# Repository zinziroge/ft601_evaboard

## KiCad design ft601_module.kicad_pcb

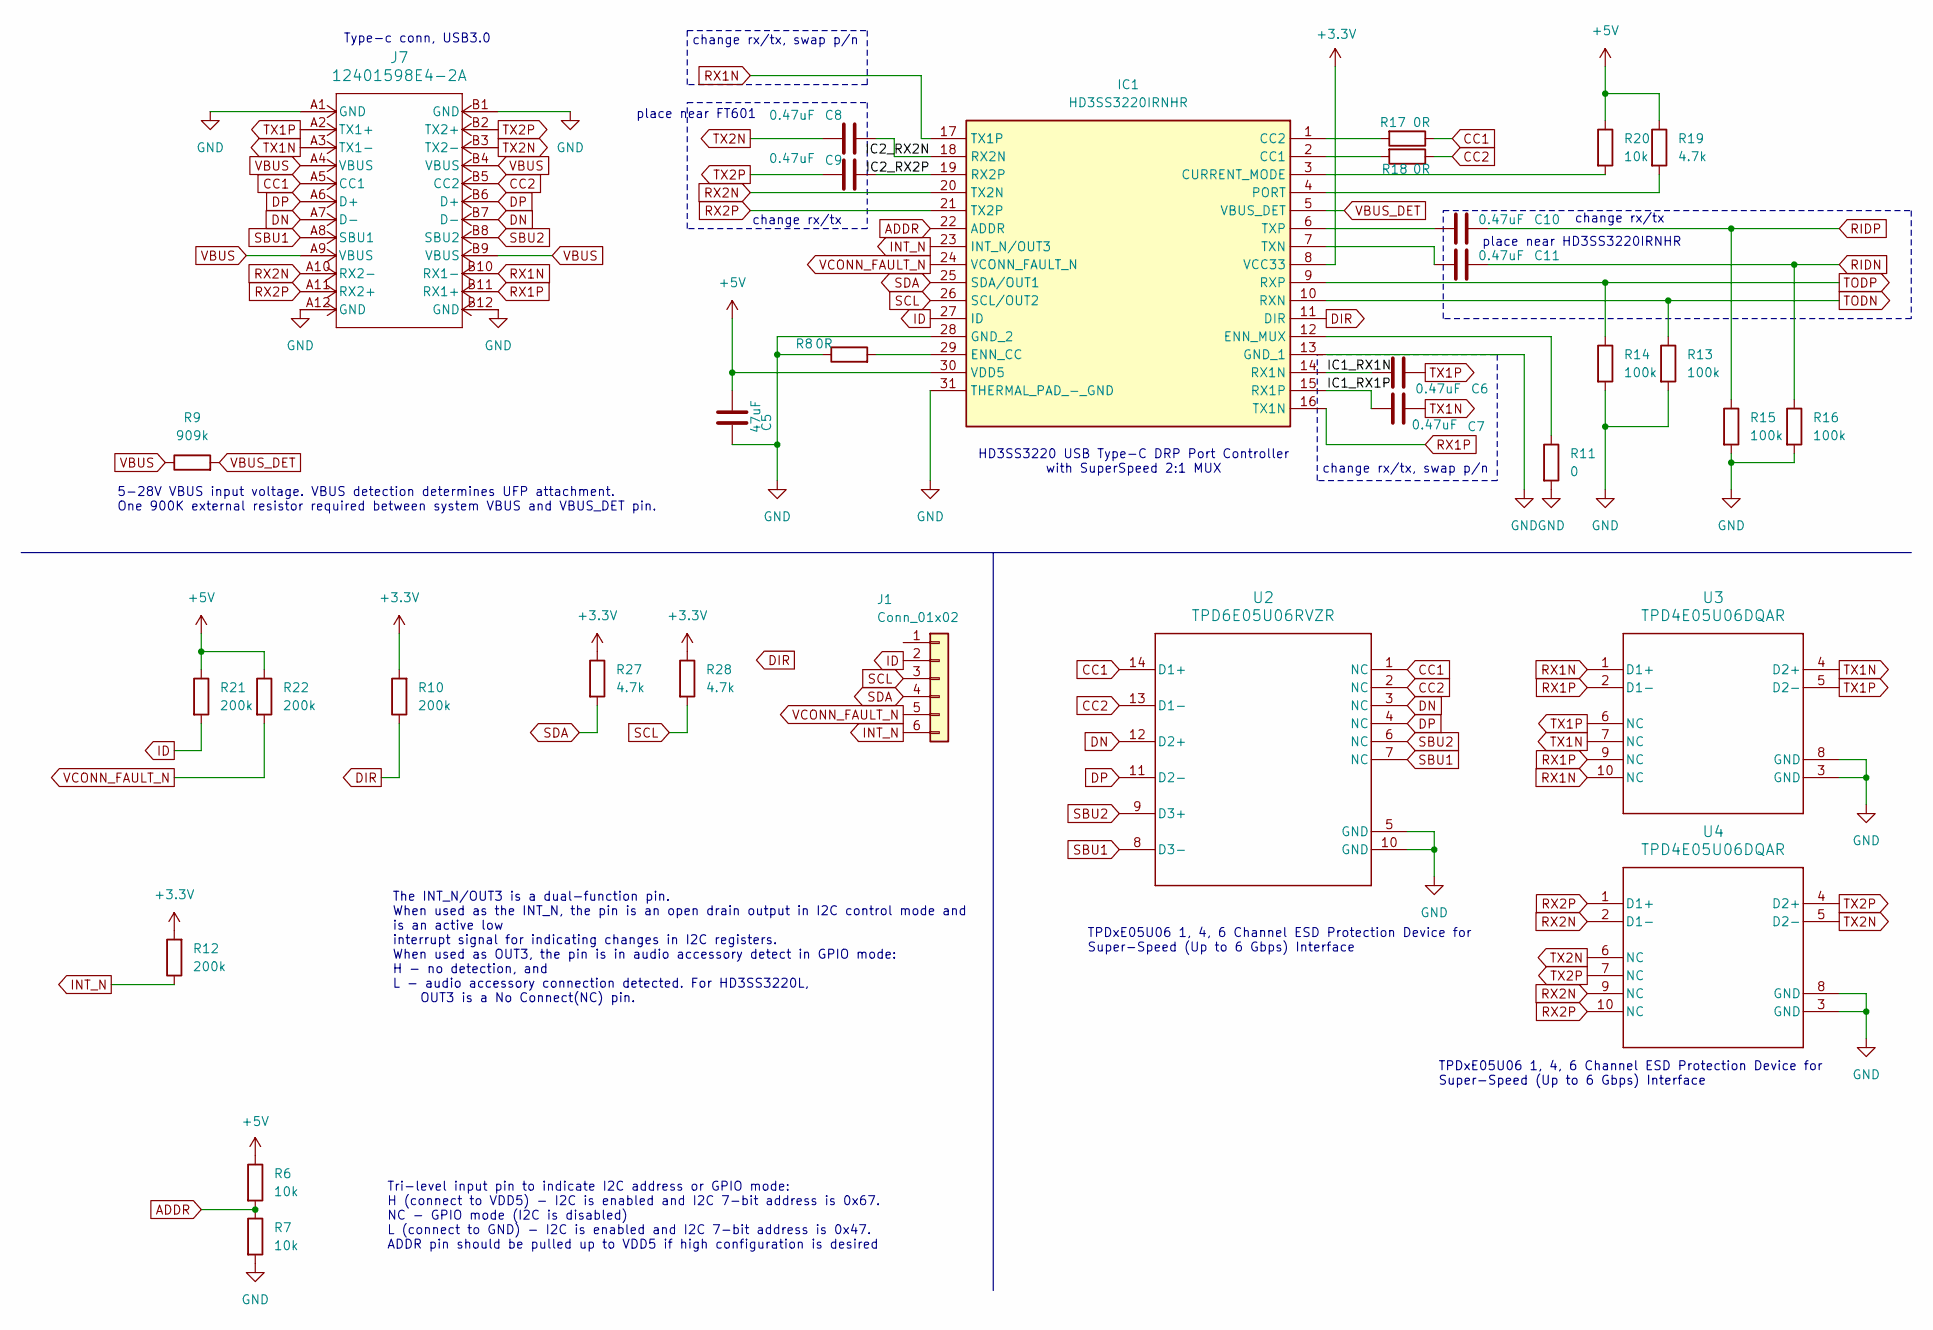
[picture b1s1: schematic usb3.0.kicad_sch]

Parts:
C5: 47uF; C_0603_1608Metric
C6, C7, C8, C9, C10, C11: 0.47uF; C_0402_1005Metric
IC1: HD3SS3220IRNHR; Manufacturer_Part_Number HD3SS3220IRNHR; Mouser Part Number 595-HD3SS3220IRNHR
J1: Conn_01x02; PinHeader_1x06_P2.54mm_Vertical
J7: 12401598E4-2A; CONN_12401598E4-2A_AMP
R6, R7, R20: 10k; R_0603_1608Metric
R8, R17, R18: 0R; R_0603_1608Metric
R9: 909k; R_0603_1608Metric
R10, R12, R21, R22: 200k; R_0603_1608Metric
R11: 0; R_0603_1608Metric
R13, R14, R15, R16: 100k; R_0603_1608Metric
R19, R27, R28: 4.7k; R_0603_1608Metric
U2: TPD6E05U06RVZR; RVZ0014A
U3, U4: TPD4E05U06DQAR; DQA0010A

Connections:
+3.3V: IC1.8 (VCC33), R10.2, R12.2, R27.1, R28.1; also elsewhere on the board
+5V: C5.1, IC1.30 (VDD5), R6.1, R19.1, R20.1, R21.1, R22.1; also elsewhere on the board
/usb3.0/IC1_RX1N: C6.2, IC1.14 (RX1N)
/usb3.0/IC1_RX1P: C7.2, IC1.15 (RX1P)
/usb3.0/IC2_RX2N: C8.1, IC1.18 (RX2N)
/usb3.0/IC2_RX2P: C9.1, IC1.19 (RX2P)
ADDR: IC1.22 (ADDR), R6.2, R7.1
CC1: J7.A5 (CC1), R17.1, U2.1 (NC), U2.14 (D1+)
CC2: J7.B5 (CC2), R18.1, U2.2 (NC), U2.13 (D1-)
DIR: IC1.11 (DIR), R10.1
DN: J7.A7 (D-), J7.B7 (D-), U2.3 (NC), U2.12 (D2+); also elsewhere on the board
DP: J7.A6 (D+), J7.B6 (D+), U2.4 (NC), U2.11 (D2-); also elsewhere on the board
GND: C5.2, IC1.13 (GND_1), IC1.28 (GND_2), IC1.31 (THERMAL_PAD_-_GND), J7.A1 (GND), J7.A12 (GND), J7.B1 (GND), J7.B12 (GND), R7.2, R8.1, R11.2, R13.2, R14.2, R15.2, R16.2, U2.5 (GND), U2.10 (GND), U3.3 (GND), U3.8 (GND), U4.3 (GND), U4.8 (GND); also elsewhere on the board
ID: IC1.27 (ID), J1.2, R21.2
INT_N: IC1.23 (INT_N/OUT3), J1.6, R12.1
unnamed: IC1.2 (CC1), R18.2
unnamed: IC1.1 (CC2), R17.2
unnamed: IC1.3 (CURRENT_MODE), R20.2
unnamed: IC1.29 (ENN_CC), R8.2
unnamed: IC1.12 (ENN_MUX), R11.1
unnamed: IC1.4 (PORT), R19.2
unnamed: C11.2, IC1.7 (TXN)
unnamed: C10.2, IC1.6 (TXP)
RIDN: C11.1, R16.1; also elsewhere on the board
RIDP: C10.1, R15.1; also elsewhere on the board
RX1N: IC1.17 (TX1P), J7.B10 (RX1-), U3.1 (D1+), U3.10 (NC)
RX1P: IC1.16 (TX1N), J7.B11 (RX1+), U3.2 (D1-), U3.9 (NC)
RX2N: IC1.20 (TX2N), J7.A10 (RX2-), U4.2 (D1-), U4.9 (NC)
RX2P: IC1.21 (TX2P), J7.A11 (RX2+), U4.1 (D1+), U4.10 (NC)
SBU1: J7.A8 (SBU1), U2.7 (NC), U2.8 (D3-)
SBU2: J7.B8 (SBU2), U2.6 (NC), U2.9 (D3+)
SCL: IC1.26 (SCL/OUT2), J1.3, R28.2
SDA: IC1.25 (SDA/OUT1), J1.4, R27.2
TODN: IC1.10 (RXN), R13.1; also elsewhere on the board
TODP: IC1.9 (RXP), R14.1; also elsewhere on the board
TX1N: C7.1, J7.A3 (TX1-), U3.4 (D2+), U3.7 (NC)
TX1P: C6.1, J7.A2 (TX1+), U3.5 (D2-), U3.6 (NC)
TX2N: C8.2, J7.B3 (TX2-), U4.5 (D2-), U4.6 (NC)
TX2P: C9.2, J7.B2 (TX2+), U4.4 (D2+), U4.7 (NC)
VBUS: J7.A4 (VBUS), J7.A9 (VBUS), J7.B4 (VBUS), J7.B9 (VBUS), R9.1; also elsewhere on the board
VBUS_DET: IC1.5 (VBUS_DET), R9.2
VCONN_FAULT_N: IC1.24 (VCONN_FAULT_N), J1.5, R22.2

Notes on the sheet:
place near FT601
HD3SS3220 USB Type-C DRP Port Controller with SuperSpeed 2:1 MUX
change rx/tx, swap p/n
5-28V VBUS input voltage. VBUS detection determines UFP attachment. One 900K external resistor required between system VBUS and VBUS_DET pin.
The INT_N/OUT3 is a dual-function pin. When used as the INT_N, the pin is an open drain output in I2C control mode and is an active low interrupt signal for indicating changes in I2C registers. When used as OUT3, the pin is in audio accessory detect in GPIO mode: H - no detection, and L - audio acc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
change rx/tx
TPDxE05U06 1, 4, 6 Channel ESD Protection Device for Super-Speed (Up to 6 Gbps) Interface
Tri-level input pin to indicate I2C address or GPIO mode: H (connect to VDD5) - I2C is enabled and I2C 7-bit address is 0x67. NC - GPIO mode (I2C is disabled) L (connect to GND) - I2C is enabled and I2C 7-bit address is 0x47. ADDR pin should be pulled up to VDD5 if high configuration is desired
Type-c conn, USB3.0
place near HD3SS3220IRNHR
TPDxE05U06 1, 4, 6 Channel ESD Protection Device for Super-Speed (Up to 6 Gbps) Interface

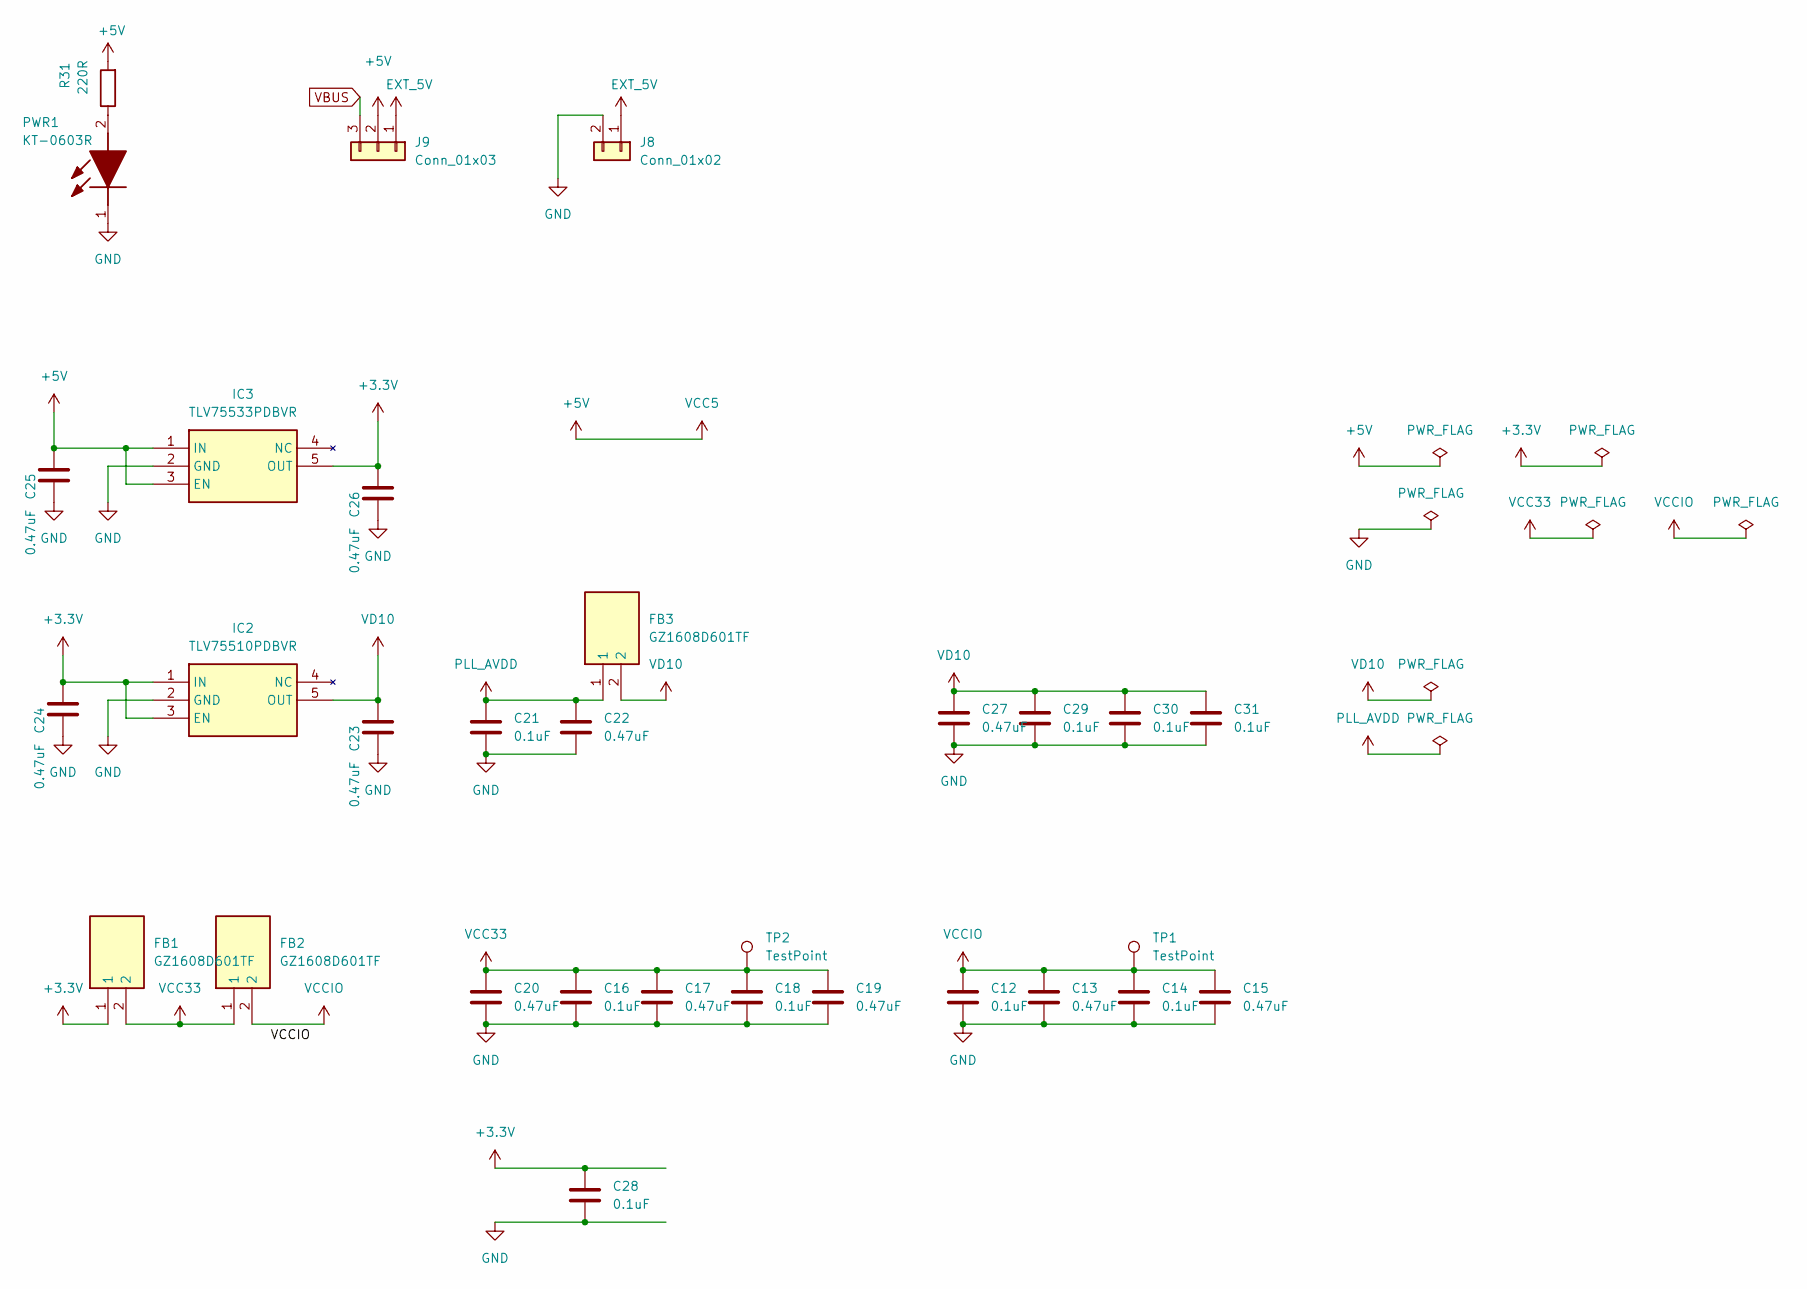
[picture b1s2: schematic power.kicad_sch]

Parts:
C12, C14, C16, C18, C21, C28, C29, C30, C31: 0.1uF; C_0603_1608Metric
C13, C15, C17, C19, C20, C22, C27: 0.47uF; C_0603_1608Metric
C23, C24, C25, C26: 0.47uF; C_0402_1005Metric
FB1, FB2, FB3: GZ1608D601TF; BEADC1608X95N; Manufacturer_Part_Number GZ1608D601TF
IC2: TLV75510PDBVR; SOT95P280X145-5N; Manufacturer_Part_Number TLV75510PDBVR; Mouser Part Number 595-TLV75510PDBVR
IC3: TLV75533PDBVR; SOT95P280X145-5N; Manufacturer_Part_Number TLV75533PDBVR; Mouser Part Number 595-TLV75533PDBVR
J8: Conn_01x02; PinHeader_1x02_P2.54mm_Vertical
J9: Conn_01x03; PinSocket_1x03_P2.54mm_Vertical
PWR1: KT-0603R; LEDC1608X70N; Manufacturer_Part_Number KT-0603R
R31: 220R; R_0603_1608Metric
TP1, TP2: TestPoint; TestPoint_Pad_D1.5mm

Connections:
+3.3V: C24.1, C26.1, C28.1, FB1.1, IC2.1 (IN), IC2.3 (EN), IC3.5 (OUT); also elsewhere on the board
+5V: C25.1, IC3.1 (IN), IC3.3 (EN), J9.2, R31.2; also elsewhere on the board
EXT_5V: J8.1, J9.1
GND: C12.2, C13.2, C14.2, C15.2, C16.2, C17.2, C18.2, C19.2, C20.2, C21.2, C22.2, C23.2, C24.2, C25.2, C26.2, C27.2, C28.2, C29.2, C30.2, C31.2, IC2.2 (GND), IC3.2 (GND), J8.2, PWR1.1 (K); also elsewhere on the board
unnamed: PWR1.2 (A), R31.1
PLL_AVDD: C21.1, C22.1, FB3.1; also elsewhere on the board
VBUS: J9.3; also elsewhere on the board
VCC33: C16.1, C17.1, C18.1, C19.1, C20.1, FB1.2, FB2.1, TP2.1; also elsewhere on the board
VCCIO: C12.1, C13.1, C14.1, C15.1, FB2.2, TP1.1; also elsewhere on the board
VD10: C23.1, C27.1, C29.1, C30.1, C31.1, FB3.2, IC2.5 (OUT); also elsewhere on the board

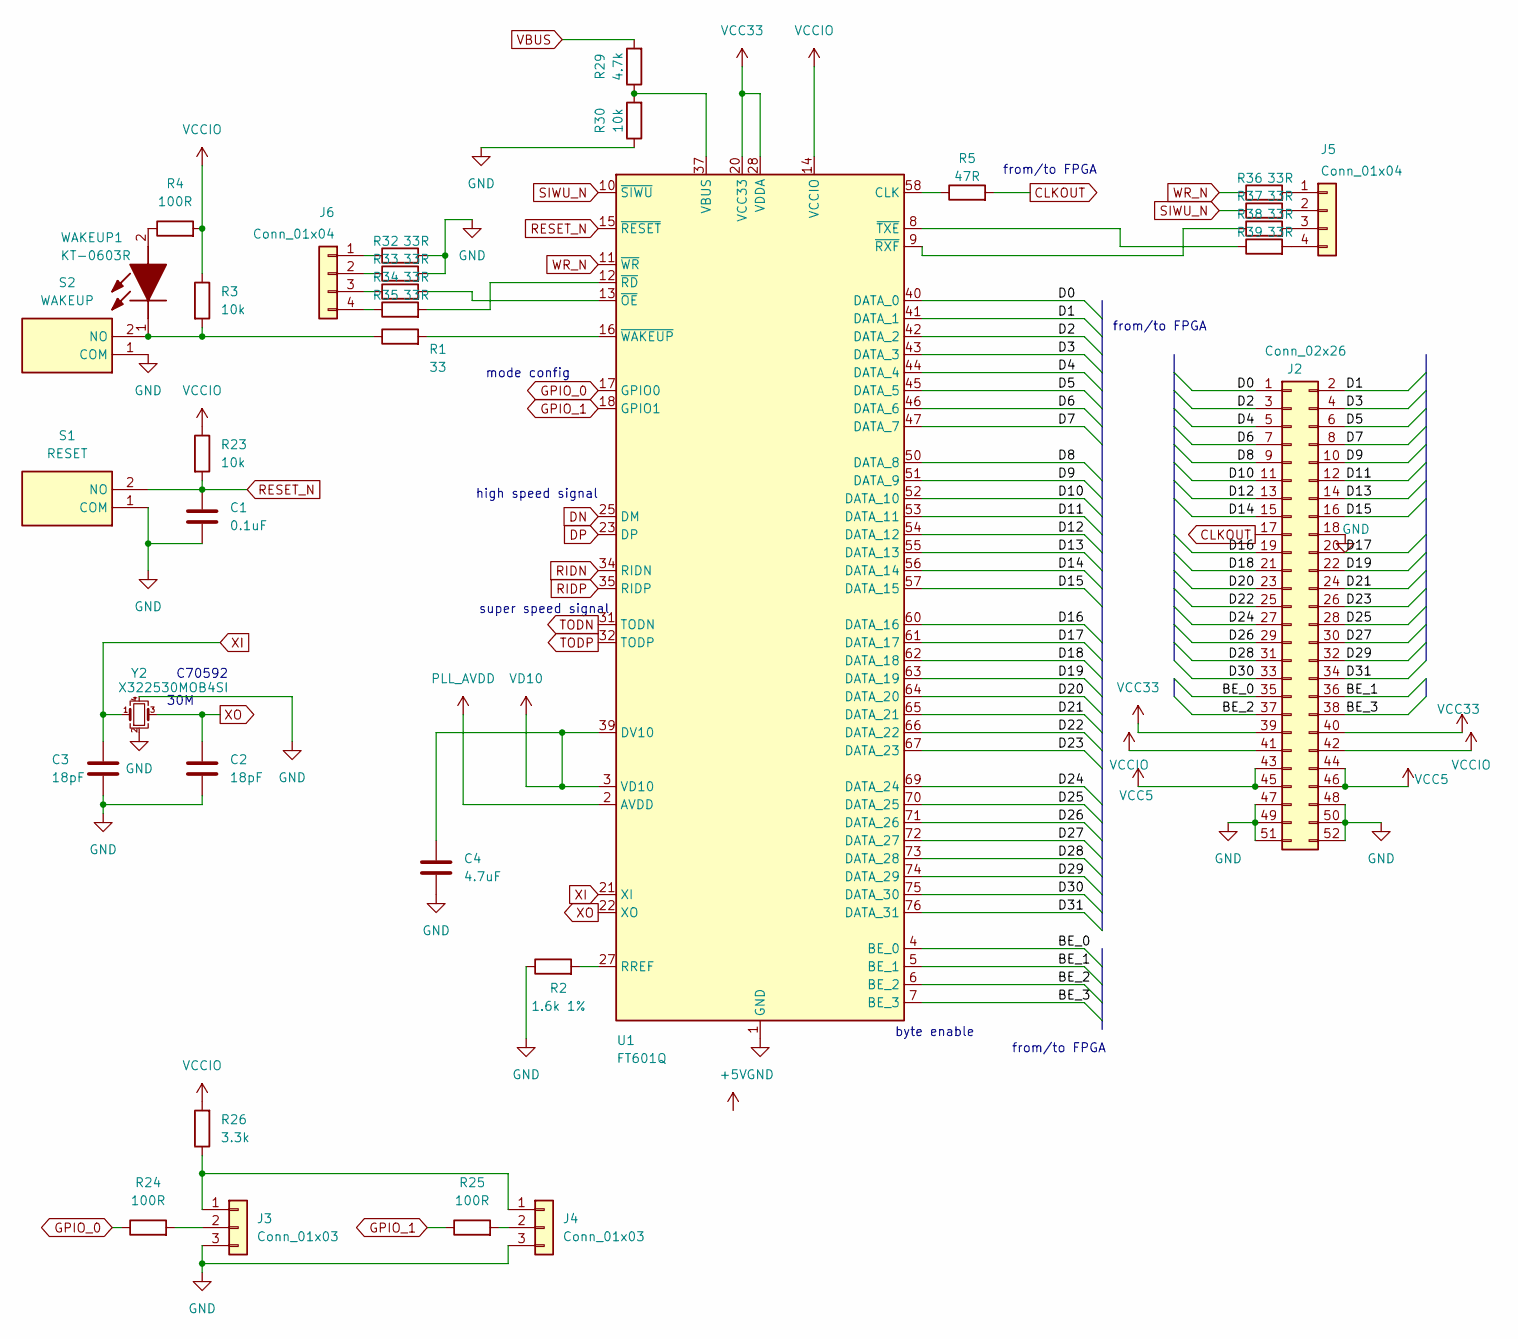
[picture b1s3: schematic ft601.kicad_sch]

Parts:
C1: 0.1uF; C_0603_1608Metric
C2, C3: 18pF; C_0603_1608Metric
C4: 4.7uF; C_0603_1608Metric
J2: Conn_02x26; PinSocket_2x26_P2.54mm_Vertical
J3, J4: Conn_01x03; PinHeader_1x03_P2.54mm_Vertical
J5, J6: Conn_01x04; PinHeader_1x04_P2.54mm_Vertical
R1: 33; R_0603_1608Metric
R2: 1.6k 1%; R_0603_1608Metric
R3, R23, R30: 10k; R_0603_1608Metric
R4, R24, R25: 100R; R_0603_1608Metric
R5: 47R; R_0603_1608Metric
R26: 3.3k; R_0603_1608Metric
R29: 4.7k; R_0603_1608Metric
R32, R33, R34, R35, R36, R37, R38, R39: 33R; R_0603_1608Metric
S1: RESET; TS1088AR02016; Manufacturer_Part_Number TS-1088-AR02016
S2: WAKEUP; TS1088AR02016; Manufacturer_Part_Number TS-1088-AR02016
U1: FT601Q; QFN-76-1EP_9x9mm_P0.4mm_EP5.81x6.31mm
WAKEUP1: KT-0603R; LEDC1608X70N; Manufacturer_Part_Number KT-0603R
Y2: X322530MOB4SI; Oscillator_SMD_YXC_X322530MOB4SI_SMD3225_4pin

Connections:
+5V: J2.43, J2.44, J2.45, J2.46; also elsewhere on the board
/ft601/BE_0: J2.35, U1.4 (BE_0)
/ft601/BE_1: J2.36, U1.5 (BE_1)
/ft601/BE_2: J2.37, U1.6 (BE_2)
/ft601/BE_3: J2.38, U1.7 (BE_3)
/ft601/D0: J2.1, U1.40 (DATA_0)
/ft601/D1: J2.2, U1.41 (DATA_1)
/ft601/D2: J2.3, U1.42 (DATA_2)
/ft601/D3: J2.4, U1.43 (DATA_3)
/ft601/D4: J2.5, U1.44 (DATA_4)
/ft601/D5: J2.6, U1.45 (DATA_5)
/ft601/D6: J2.7, U1.46 (DATA_6)
/ft601/D7: J2.8, U1.47 (DATA_7)
/ft601/D8: J2.9, U1.50 (DATA_8)
/ft601/D9: J2.10, U1.51 (DATA_9)
/ft601/D10: J2.11, U1.52 (DATA_10)
/ft601/D11: J2.12, U1.53 (DATA_11)
/ft601/D12: J2.13, U1.54 (DATA_12)
/ft601/D13: J2.14, U1.55 (DATA_13)
/ft601/D14: J2.15, U1.56 (DATA_14)
/ft601/D15: J2.16, U1.57 (DATA_15)
/ft601/D16: J2.19, U1.60 (DATA_16)
/ft601/D17: J2.20, U1.61 (DATA_17)
/ft601/D18: J2.21, U1.62 (DATA_18)
/ft601/D19: J2.22, U1.63 (DATA_19)
/ft601/D20: J2.23, U1.64 (DATA_20)
/ft601/D21: J2.24, U1.65 (DATA_21)
/ft601/D22: J2.25, U1.66 (DATA_22)
/ft601/D23: J2.26, U1.67 (DATA_23)
/ft601/D24: J2.27, U1.69 (DATA_24)
/ft601/D25: J2.28, U1.70 (DATA_25)
/ft601/D26: J2.29, U1.71 (DATA_26)
/ft601/D27: J2.30, U1.72 (DATA_27)
/ft601/D28: J2.31, U1.73 (DATA_28)
/ft601/D29: J2.32, U1.74 (DATA_29)
/ft601/D30: J2.33, U1.75 (DATA_30)
/ft601/D31: J2.34, U1.76 (DATA_31)
CLKOUT: J2.17, R5.2
DN: U1.25 (DM); also elsewhere on the board
DP: U1.23 (DP); also elsewhere on the board
GND: C1.2, C2.2, C3.2, C4.2, J2.18, J2.47, J2.48, J2.49, J2.50, J2.51, J2.52, J3.3, J4.3, R2.1, R30.1, R32.2, R33.2, S1.1 (COM), S2.1 (COM), U1.1 (GND), U1.26 (GND), U1.29 (GND), U1.36 (GND), U1.77 (GND), Y2.2, Y2.4; also elsewhere on the board
GPIO_0: R24.1, U1.17 (GPIO0)
GPIO_1: R25.1, U1.18 (GPIO1)
unnamed: J3.1, J4.1, R26.1
unnamed: J3.2, R24.2
unnamed: J4.2, R25.2
unnamed: J5.1, R36.2
unnamed: J5.2, R37.2
unnamed: J5.3, R38.2
unnamed: J5.4, R39.2
unnamed: J6.1, R32.1
unnamed: J6.2, R33.1
unnamed: J6.3, R34.1
unnamed: J6.4, R35.1
unnamed: R1.1, R3.2, S2.2 (NO), WAKEUP1.1 (K)
unnamed: R5.1, U1.58 (CLK)
unnamed: R2.2, U1.27 (RREF)
unnamed: R29.1, R30.2, U1.37 (VBUS)
unnamed: R34.2, U1.13 (~OE)
unnamed: R35.2, U1.12 (~RD)
unnamed: R38.1, U1.9 (~RXF)
unnamed: R39.1, U1.8 (~TXE)
unnamed: R1.2, U1.16 (~WAKEUP)
unnamed: R4.1, WAKEUP1.2 (A)
PLL_AVDD: U1.2 (AVDD); also elsewhere on the board
RESET_N: C1.1, R23.2, S1.2 (NO), U1.15 (~RESET)
RIDN: U1.34 (RIDN); also elsewhere on the board
RIDP: U1.35 (RIDP); also elsewhere on the board
SIWU_N: R37.1, U1.10 (~SIWU)
TODN: U1.31 (TODN); also elsewhere on the board
TODP: U1.32 (TODP); also elsewhere on the board
VBUS: R29.2; also elsewhere on the board
VCC33: J2.39, J2.40, U1.20 (VCC33), U1.24 (VCC33), U1.28 (VDDA), U1.38 (VCC33); also elsewhere on the board
VCCIO: J2.41, J2.42, R3.1, R4.2, R23.1, R26.2, U1.14 (VCCIO), U1.49 (VCCIO), U1.59 (VCCIO), U1.68 (VCCIO); also elsewhere on the board
VD10: C4.1, U1.3 (VD10), U1.30 (VD10), U1.33 (VD10), U1.39 (DV10), U1.48 (VD10); also elsewhere on the board
WR_N: R36.1, U1.11 (~WR)
XI: C3.1, U1.21 (XI), Y2.1
XO: C2.1, U1.22 (XO), Y2.3

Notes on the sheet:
C70592
from/to FPGA
super speed signal
30M
mode config
high speed signal
byte enable

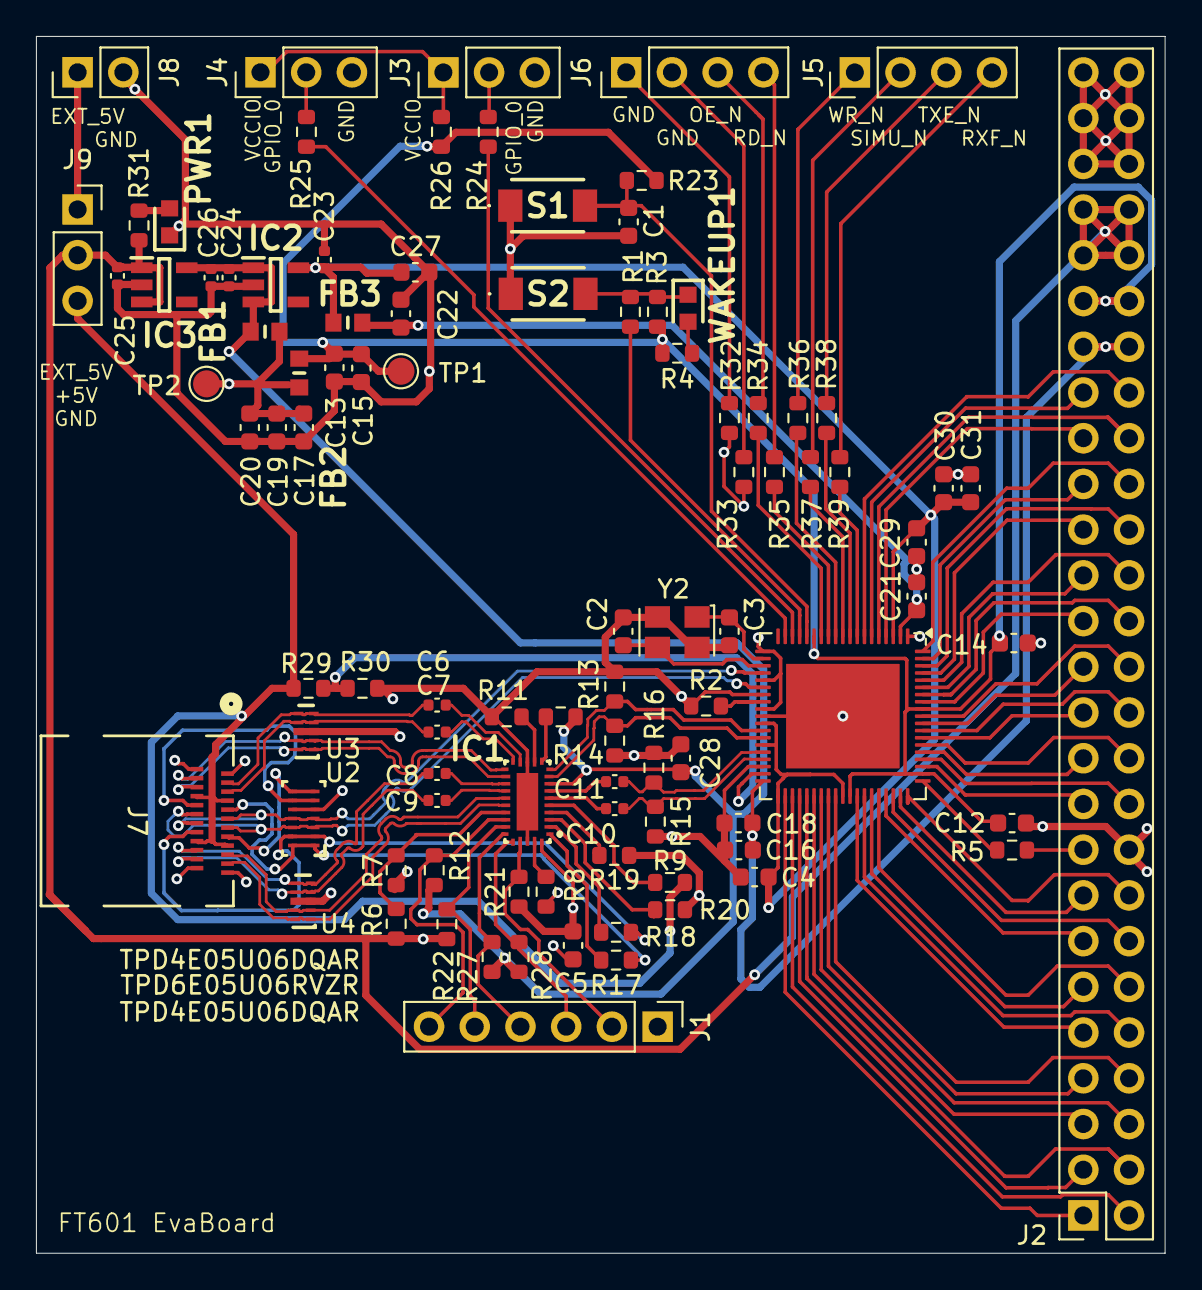
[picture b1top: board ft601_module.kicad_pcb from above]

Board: 4 copper layers, 62.7 x 67.6 mm, 96 parts (0 on the bottom side), 113 nets.

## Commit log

2026-03-01 JLCPCB order. W2026020708395445
